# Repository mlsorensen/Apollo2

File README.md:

# Apollo 2

<!-- One logo for both GitHub themes: dark ink on a solid white silhouette
     with a white halo around the outside, so it reads on white (fill and halo
     invisible) and on a dark page (a light bust with a glow). A <picture> +
     prefers-color-scheme switch was tried and follows the BROWSER's colour
     scheme, not the GitHub theme: Safari on a dark-mode Mac served the white
     logo onto a light GitHub page. -->

Firmware project that turns a small ESP32 touchscreen into a local
controller for a **La Marzocco Micra** espresso machine — over Bluetooth, with
no cloud dependency for day‑to‑day use.

Set your brew temperature, flip the steam boiler, put the machine on standby,
watch the boiler come up to temperature, and (with a supported Bluetooth scale)
run a live shot timer and flow graph — all from a dedicated little screen next
to the machine instead of a phone app.

> The focus is on local control via bluetooth. Currently internet is only used for optional NTP.

**Contents:**
[Features](#features) ·
[Getting started](#getting-started) ·
[Screenshots](#screenshots) ·
[Supported hardware](#supported-hardware) ·
[3D prints](#3d-prints) ·
[Developer documentation](#developer-documentation) ·
[Credits](#credits) ·
[License](#license)

---

## Features

- **Local Micra control over Bluetooth** — brew and steam temperatures, steam
  boiler on/off, standby, and live machine status. No cloud, no phone app.
- **Bluetooth scales** — Bookoo Themis, Acaia (Umbra, Lunar, Prochef, Pyxis)
  and Varia Aku: live weight, shot timer, flow graph, tare, and the scale's
  own settings from the screen. A second, **bench** scale for the counter
  shows its weight on Home too — in the scale card or beside the graph —
  and, with **Record dose** turned on, records your dose for the next shot
  (or set a default dose), so the graph and History show the brew ratio.
- **Brew by weight** — stop the shot at a target weight on boards wired into
  the paddle circuit, or detect shots from the weight stream alone on any
  board. Finished shots freeze into a review graph.
- **Group care** — auto‑flush after the cup lifts, flush on demand, and a
  backflush cleaning cycle, on wired boards.
- **Warm‑up chime** — boards with a speaker play a tune when the machine is
  ready, so you can start it and walk away.
- **Schedule** — switch the machine on (with a warm‑up lead) and back to
  standby at set times, the same every day or per weekday, from the device's
  own NTP clock. **Auto‑standby** sends it to standby a set time after the
  last shot, independent of the schedule.
- **Shot history** — every shot is saved to a microSD card as CSV, browsable on
  the device's Stats tab or from a phone via the device's own web page.
- **Settings backup** — preferences copy to the same card and restore onto
  replacement hardware.
- **Over‑the‑air updates** — the device checks for new firmware and installs
  it on request, with an optional beta channel.
- **Setup from your phone, no app** — pairing and Wi‑Fi credentials go in
  through a page the device serves itself; scan the QR code on its screen.
- **Automatic time** — NTP over your Wi‑Fi with a timezone picker, saved to
  the on‑board RTC where present.
- **Made to live on the counter** — themes, °C/°F, 12/24‑hour clock,
  brightness, idle‑screen artwork; layouts from 4.3" to 8" panels.

Everything keeps working if the machine, the scale, or Wi‑Fi is absent — the
UI just shows that part as offline.

---

## Getting started

> [!IMPORTANT]
> **Before buying any hardware, confirm you can get your machine's Bluetooth
> token.** Apollo authenticates to the Micra with a token issued by the La
> Marzocco cloud. Grab it first with the **[LM Token](tools/lmtoken/)** app — sign
> in with your La Marzocco account and copy the token. If it comes back blank, the
> same tool can provision one over Bluetooth. Checking now avoids a nasty surprise
> after a board is already on your bench.

**Prefer to watch?** [Apollo 2 for Micra — From Setup to Shot](https://youtu.be/2J9Y8xyeB9w)
walks through choosing a board, flashing it and setting it up, start to first shot.

### 1. Get the hardware

Pick a board from the **[Which board?](#which-board)** table below — three of
them come as finished boxes that need no assembly at all. A Bluetooth scale is
optional but unlocks the shot timer, flow graph, and brew‑by‑weight. Wiring
the machine's paddle (for Auto shot) is optional too, and can always be added
later — see the [wiring guide](docs/WIRING.md) (which also covers the
optional Apollo Link board — **P4 boards only**, not the S3‑4.3C).

### 2. Flash the firmware

**No-toolchain option:** the [web flasher](https://mlsorensen.github.io/Apollo2/)
flashes any supported board straight from Chrome, Edge, or Firefox over USB —
pick your board, click Install. (The P4‑5 and P4‑4.3 exist with two ESP32‑P4
chip revisions that need different images; boards bought before about August
2026 are v1.x, newer ones v3. **Detect board** reads it off a device already
running Apollo; on a blank board pick it on the card. A wrong pick just won't
boot until the other image is flashed.) Upgrading this way keeps your paired machine,
Wi‑Fi and settings (unless you choose "Erase device"). Prebuilt images also live
on the [Releases](https://github.com/mlsorensen/Apollo2/releases) page — those
are full images, so flashing one with `esptool` *does* clear saved settings.

Until a Micra is paired, the device opens on a welcome screen with the three
recommended steps: **Set up WiFi** (network and time zone from your phone;
sets the clock and enables updates), **Pair Micra**, and **Pair scale**. All
are optional — **Later** skips it until the next power‑up, **Don't show
again** for good; every step is in Settings too.

After the first flash Apollo updates itself over WiFi: it checks for new
firmware, shows what changed, and installs on a tap. Tick **Include
pre-releases** on the flasher (or turn on **Settings → Apollo → WiFi → Beta
updates** on the device) to run beta builds instead — testing welcome, and a
build that won't boot rolls back on its own.

Building from source requires [PlatformIO](https://platformio.org/) (`pio`) and
a USB cable.

```sh
make flash            # print selection of flash options
make flash-p4-5       # or target a board: p4-5 | p4-4-3 | s3-4-3c | p4-x-8
                      # (P4-5 / P4-4.3 come with two chip revisions needing different
                      #  images; these targets read the chip and pick the right one)
make monitor          # open the serial console (115200 baud)
```

### 3. Pair the machine

**Settings → Micra → Bluetooth → Scan**, then pick your machine. The device saves
it, then asks for the machine's **Bluetooth token** (step 4) — the token is issued
by the La Marzocco cloud and can't be read off the machine, so there's a short
one‑time step to fetch it.

### 4. Enter your token

Tap **Enter token** on the prompt (or **Settings → Micra → Set up**) to start the
device's own Wi‑Fi access point, **`Micra-Setup`**. Scan the QR code on the
device's screen with your phone's camera — it joins the access point and the
setup page pops up on its own. (Or join `Micra-Setup` manually and open
**http://192.168.4.1**.) Paste your token and Save — the device connects and the
access point closes on its own.

Where to get the token:

- Download the **LM Token** app for your OS from the [Releases](../../releases)
  page, unzip, and double-click it. Sign in with your La Marzocco account, pick
  your machine, and hit **Copy token**. This is the only step that uses the
  internet, and it runs on your computer. (Prefer a terminal? The `lmtoken` CLI
  is on the same page.)

> Prefer to build **LM Token** / `lmtoken` from source (Go), or script it? See
> [`tools/lmtoken/README.md`](tools/lmtoken/README.md).

### 5. (Optional) Wi‑Fi + automatic time

On the same setup page you can enter your home Wi‑Fi name and password. The
device then joins your network, gets an IP, and syncs the clock over NTP. Pick
your city under **Settings → Apollo → WiFi → Timezone**. Auto‑sync can be turned
off there too (**Auto time (NTP)**).

Because the setup page is always reachable from **Set up WiFi**, you can never be
locked out if your network changes.

### 6. Find your way around

- **Home** shows the machine (and scale, if paired). The large action button is
  Standby / Turn On when connected, and becomes a **Connect** button when the
  machine is disconnected. With a scale, the pill under the shot timer cycles
  the shot mode — **Auto shot** (wired paddle boards) / **Shot detect** /
  **Manual** — and becomes **Reset** while a finished shot is up for review.
- **Settings** groups everything under Micra, Scale, and Device (brightness,
  clock, units, theme, Wi‑Fi).
- **Stats** shows brew/boiler temperature history, the shot **History** log
  (SD‑card boards), and device info.

Every screen and setting is described in the **[user manual](MANUAL.md)** —
it opens with a **map of every screen and setting** if you're looking for
where something lives.

---

## Screenshots

<!-- These are curated copies of the simulator's output — see "The simulator"
     under Developer documentation for the refresh convention. -->

---

## Supported hardware

The firmware targets Waveshare ESP32 touch boards. One board is selected at
build time.

### Which board?

Four boards are supported, and each has its own firmware image. Every one of
them delivers the full brew‑by‑weight experience with **zero wiring** (via Shot
detect); the wiring column only matters if you *also* want **Auto shot** — the
wired‑paddle mode where the machine's own paddle starts the shot and the
firmware cuts it at target weight.

| Pick | Best for | Screen | Enclosure | Auto‑shot wiring *(optional)* | Performance |
|------|----------|--------|-----------|-------------------------------|-------------|
| [ESP32‑P4‑WIFI6‑Touch‑LCD‑5](https://www.waveshare.com/esp32-p4-wifi6-touch-lcd-5.htm) (SKU 33762) | **Mounting on the Micra** | 5" 1280×720 | [3D‑printed shell](hardware/3d-prints/) | DIY cable with an external opto module | **Best** |
| [ESP32‑P4‑WIFI6‑Touch‑LCD‑4.3](https://www.waveshare.com/esp32-p4-wifi6-touch-lcd-4.3.htm) | **Mounting on the Micra, smaller screen** | 4.3" 800×480 | [3D‑printed shell](hardware/3d-prints/) | DIY cable with an external opto module | **Best** |
| [ESP32‑S3‑Touch‑LCD‑4.3C **BOX**](https://www.waveshare.com/esp32-s3-touch-lcd-4.3c.htm?sku=33630) (SKU 33630) | **Mounting on the Micra with nothing to build** | 4.3" 800×480 | Finished box | **Built‑in opto** — three wires into screw terminals, nothing to build (the optional Apollo Link board is P4‑only and does not fit this box) | Good |
| [ESP32‑P4‑WIFI6‑Touch‑LCD‑X **8" box**](https://www.waveshare.com/esp32-p4-wifi6-touch-lcd-7-8-10.1.htm) | **Counter‑top companion** | 8" 1280×800 | Finished box | DIY cable with an external opto module | **Best** |

**Start with the ESP32‑P4‑WIFI6‑Touch‑LCD‑5.** It's the recommended
mount‑on‑the‑Micra option: the P4 is much faster than the S3 (32 MB flash +
32 MB PSRAM against 16/8), and the 5" panel is the right size on the machine.
The cost is two bits of DIY — you print a [shell](hardware/3d-prints/), and if
you want Auto shot you make up a cable with an external opto module.

**The ESP32‑P4‑WIFI6‑Touch‑LCD‑4.3 is the same board with a smaller screen.**
Identical electronics — same processor, radio, audio, battery path, SD slot and
paddle wiring; only the panel differs (4.3" 800×480 instead of 5" 1280×720).
Pick between the two on **screen size and a small price difference**, nothing
else. It takes its own [printed shell](hardware/3d-prints/) and its own
firmware image.

**Choose the S3‑4.3C BOX if you'd rather not print a case or build a cable.** It's the
only small board that arrives as a finished box *and* has the opto‑isolators
built in, so Auto shot is three wires into screw terminals with no cable to
assemble — genuinely the least‑hacking route to a fully wired setup. The
trade is speed: it's the slower part. (The [wiring guide](docs/WIRING.md)
covers both styles.)

**The X 8" box is the counter‑top companion** — the same P4 electronics behind
the biggest screen, in a finished enclosure, for sitting beside the machine
rather than on it. Verified on hardware.

Power, battery and RTC notes live in
**[docs/HARDWARE.md](docs/HARDWARE.md)**.

### 3D‑printed stand, shells and mounts

Ready‑to‑print 3MF files live in [`hardware/3d-prints/`](hardware/3d-prints/):

| File | What it is |
|------|------------|
| [`apollo2-stand.3mf`](hardware/3d-prints/apollo2-stand.3mf) | Counter‑top **stand**. Mounts the S3‑4.3C‑BOX directly (it has the matching holes), and every shell below mounts to it the same way. |
| [`apollo2-magnet-mount.3mf`](hardware/3d-prints/apollo2-magnet-mount.3mf) | Optional **magnet mount** — attaches the device to the Micra's top corner instead of the counter. |
| [`apollo2-wiring-gasket.3mf`](hardware/3d-prints/apollo2-wiring-gasket.3mf) | Optional **wiring gasket** — spaces the Micra's cover so the wiring can run underneath it. |
| [`esp32-p4-5-shell.3mf`](hardware/3d-prints/esp32-p4-5-shell.3mf) | Shell for the **ESP32‑P4‑WIFI6‑Touch‑LCD‑5**. |
| [`esp32-p4-5-shell-slim.3mf`](hardware/3d-prints/esp32-p4-5-shell-slim.3mf) | Slimmer shell for the **ESP32‑P4‑WIFI6‑Touch‑LCD‑5** — no battery compartment (USB‑power only). |
| [`esp32-p4-4.3-shell.3mf`](hardware/3d-prints/esp32-p4-4.3-shell.3mf) | Shell for the **ESP32‑P4‑WIFI6‑Touch‑LCD‑4.3**. |
| [`esp32-p4-x-8-backplate.3mf`](hardware/3d-prints/esp32-p4-x-8-backplate.3mf) | Backplate that adapts the **ESP32‑P4‑WIFI6‑Touch‑LCD‑X 8" box** to the counter‑top stand above. |

This [short video](https://youtube.com/shorts/Ea0IaJ7hjvQ) shows how the
magnet mount and wiring gasket fit together on the machine.

Fasteners:

- **Shells**: 8 × **M2.5×0.45, 5 mm** screws each — 4 fasten the board into
  the shell, 4 fasten the shell cover.
- **Stand mount**: 2 × **M4‑0.7×8 mm** screws — same spec whether you're
  mounting the S3‑4.3C‑BOX or any of the printed shells.
- **Magnet mount**: 8 × **10 mm × 3 mm** neodymium disc magnets.

---

## Developer documentation

### Architecture

The code is layered so the same UI runs on a real board and on a laptop:

```
include/core/        Pure interfaces (ports) + domain types. No LVGL, Arduino,
                     BLE, or SDL — just C++ and structs. e.g. IMachine, IScale,
                     IClock, INetwork, IProvisioner, IBrewController, IShotStore
                     (SD shot history), and the BLE central port (ble::ICentral).

src/core/            Portable protocol logic: the La Marzocco Micra link and
                     the Bookoo scale driver, written only against ble::ICentral
                     — so a new platform (Linux/BlueZ, Pico/btstack) reuses the
                     Bluetooth protocol code unchanged and implements only the
                     transport. Also the device-independent decisions: which
                     event makes which sound (sound.cpp), when a warm-up counts
                     as finished (ready_chime.h).

src/ui/              The LVGL user interface. Depends ONLY on core/ interfaces,
                     never on a concrete platform. Portable.

src/platform_esp32/  Device implementations of the core ports: the NimBLE GATT
                     transport, NVS config, display/touch drivers, Wi-Fi
                     station + NTP, the setup-portal web server.

src/platform_host/   "Fake" implementations that feed canned data, so the UI can
                     be built and rendered on a host with no hardware.

src/device/main.cpp  Device entry: wires the real implementations to ui::App.
src/sim/main.cpp     Simulator entry: wires the fakes, renders frames to PNG.
```

The UI is written against the `core::` ports and is injected with concrete
implementations at startup (`App::build(...)`). Swapping the real BLE machine for
a `FakeMachine` is all that separates a board build from a laptop render — the UI
code is byte‑for‑byte identical.

### The simulator

No hardware needed. Builds a native executable that renders each screen/layout
to `renders/*.png`:

```sh
make sim              # build + run, writes renders/*.png
```

This is the fastest way to iterate on UI: change code, `make sim`, look at the
PNGs. Every supported screen size and several states are rendered.

The `renders/` folder is git‑ignored build output; the screenshots in
`docs/img/` are curated copies, and the annotated manual images in
`docs/img/manual/` are generated from renders by `make docs-img`
(`tools/annotate_docs.py` + its manifest). **When the UI changes, run
`make sim`, refresh the affected `docs/img/*.png`, and re-run `make docs-img`
as part of the same change** so the README and manual stay accurate.

### Prerequisites

**PlatformIO** (`pip install platformio`) builds everything, and **node** (any
recent LTS — `brew install node`) builds the shot-history web page the device
serves. That page is embedded in the firmware as a generated header,
`include/platform_esp32/webapp_dist.h`, which is **not committed**: every
`make build`/`make flash` target rebuilds it when anything under
[`tools/webapp/`](tools/webapp) changes, and the release workflow does the same,
so a board can never serve a page that has drifted from the source. `make sim`
needs no node — the simulator has no web server.

### Building directly

`pio run` does *not* generate the web-app header (that dependency lives in the
Makefile), so run `make webapp` first — or just use the `make` targets, which
handle it.

```sh
pio run -e esp32-p4-micra-5       # 5"   1280x720 (P4, MIPI-DSI, WiFi6/BLE via C6)
pio run -e esp32-p4-micra-43      # 4.3"  800x480 (P4, MIPI-DSI, same board as the 5)
pio run -e esp32-p4-micra-5-rev3  # the same two boards on the v3 ESP32-P4 silicon
pio run -e esp32-p4-micra-43-rev3 #   (shipping since ~Aug 2026; a separate image)
pio run -e esp32-s3-micra-4-3c    # 4.3"  800x480 (S3, RGB panel)
pio run -e esp32-p4-micra-x-8     # X-series 8" box (P4, 1280x800)
pio run -e sim                    # native simulator
```

`platformio.ini` also carries a few envs for boards that aren't released — they
build, and they're kept as the record of how those boards differ. `make
build-release` compiles the six published images (four products, the two P4
boards in both silicon revisions); `make build-all` compiles
every env.

Build environments and per‑board flags live in
[`platformio.ini`](platformio.ini); the pin/panel definitions for each board are
in [`include/platform_esp32/board_config.h`](include/platform_esp32/board_config.h).

### Adding a board

Add an `#elif defined(BOARD_...)` block in `board_config.h` with the same
constant names the drivers read (pins, panel size, feature macros), then add a
matching `[env:...]` in `platformio.ini` with the `-DBOARD_...` flag. Driver code
never hardcodes a pin — it reads `board::` constants — so a new board is mostly a
config block.

That makes the board *buildable*, not *supported*. Releasing one is a separate,
deliberate step: a row in the `.github/workflows/firmware-release.yml` matrix
(whose `board` value must equal the block's `kUpdateSlug`, since the
self‑updater fetches `<site>/<tag>/firmware/app/<slug>.bin`), a card in
`site/index.html`, and a row in the tables above. (The flasher's engine,
esp-web-tools, is vendored by `tools/build_esp_web_tools.sh` with a pinned
esptool-js rather than loaded from unpkg — the script says why.) Releases are
tagged `vX.Y.Z`;
a `vX.Y.Z-beta.N` tag publishes the same images as a pre-release, listed only in
`releases-beta.json` (the stable `releases.json` every device reads stays
releases-only) — promoting one to stable is a rebuild at the real tag, never a
copy of the artifacts, because `fw::kVersion` is compiled into the image.
Publishing is gated: the workflow builds unattended, but the jobs that create
the Release and push `gh-pages` (the OTA origin) run in a protected
environment that holds the only write credential and waits for the owner's
approval, and repository rulesets let only an admin touch `gh-pages` or a
`v*` tag. Several envs stay on the
buildable side on purpose.

### Repository layout

```
include/core/          Domain interfaces + types
src/core/              Portable protocol implementations (Micra BLE, scales,
                       audio cues)
include/platform_esp32/ Device driver headers + board_config.h
include/platform_host/  Host fakes
include/ui/             UI headers (widgets, screen profiles, timezones)
include/vendor/         Vendored third-party headers (stb_image_write)
src/                    Implementations (see Architecture above)
hardware/3d-prints/     Printable stand, board shells + mounts (3MF)
docs/adr/               Decision and engineering log: why things are built
                        the way they are, with the bench evidence
tools/                  sim.sh, flash.sh, lmtoken (Go), PlatformIO helper scripts
renders/                Simulator output (PNG)
```

---

## Credits & third‑party

This project stands on the work of others. Grateful thanks to:

- **[pylamarzocco](https://github.com/zweckj/pylamarzocco)** by Josef Zweck
  (MIT) — the reference for La Marzocco's Bluetooth protocol (GATT
  characteristic UUIDs, the JSON command/state payloads, machine name prefix) and
  the cloud auth flow that `tools/lmtoken` re‑implements in Go.
- **[goscale](https://github.com/mlsorensen/goscale)** (Apache‑2.0) — the model
  for the scale interface and the Bookoo Themis notification decode.
- **[apollo](https://github.com/mlsorensen/apollo)** — brew‑by‑weight /
  paddle‑stop approach that inspires the (in‑progress) brew controller.
- **Waveshare** — board bring‑up details and register maps for the CH422G IO
  expander, GT911 / CST816 touch controllers, and the RGB panel timings, from
  their published ESP32‑S3 demos.
- **[stb_image_write](https://github.com/nothings/stb)** by Sean Barrett (public
  domain / MIT) — vendored in `include/vendor/` for PNG output in the simulator;
  its license is retained in the file.

Library dependencies (fetched by PlatformIO): **LVGL** (MIT), **NimBLE‑Arduino**
(Apache‑2.0), **Arduino‑ESP32** (LGPL‑2.1 / Apache‑2.0), **GFX Library for
Arduino** (BSD‑style), and **ArduinoJson** (MIT). Each retains its own license.

---

## License

[MIT](LICENSE) © 2026 Marcus.

Not affiliated with or endorsed by La Marzocco. "La Marzocco" and "Micra" are
trademarks of their respective owner; used here only to describe compatibility.

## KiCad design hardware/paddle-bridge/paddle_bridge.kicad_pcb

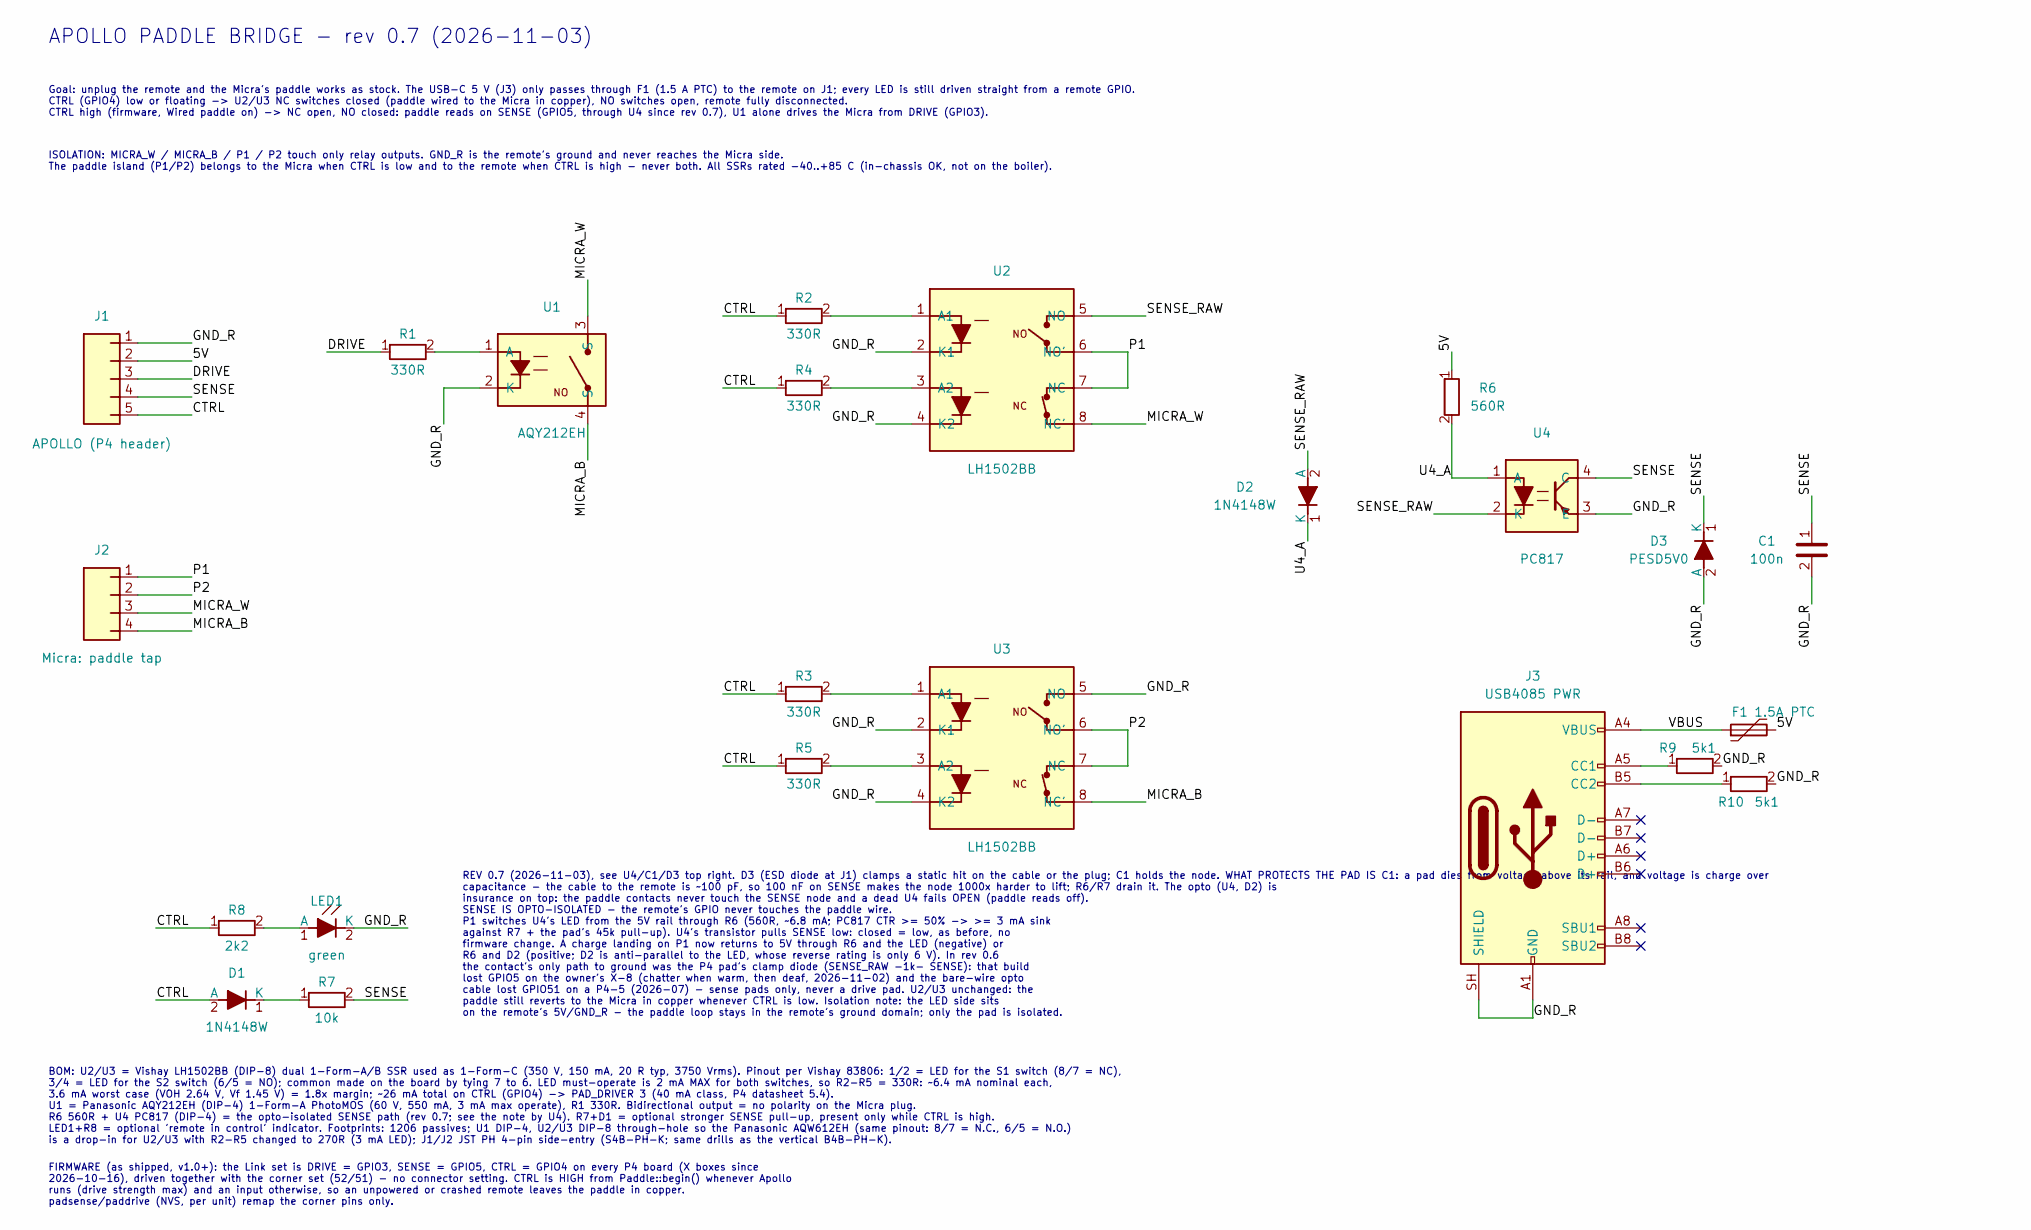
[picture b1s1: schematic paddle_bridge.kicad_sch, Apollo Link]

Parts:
C1: 100n; C_1206_3216Metric
D1, D2: 1N4148W; D_1206_3216Metric
D3: PESD5V0; D_SOD-323
F1: 1.5A PTC; Fuse_1812_4532Metric
J1: APOLLO (P4 header); JST_PH_S5B-PH-K_1x05_P2.00mm_Horizontal
J2: Micra: paddle tap; JST_PH_S4B-PH-K_1x04_P2.00mm_Horizontal
J3: USB4085 PWR; USB_C_Receptacle_GCT_USB4085
LED1: green; LED_1206_3216Metric
R1, R2, R3, R4, R5: 330R; R_1206_3216Metric
R6: 560R; R_1206_3216Metric
R7: 10k; R_1206_3216Metric
R8: 2k2; R_1206_3216Metric
R9, R10: 5k1; R_1206_3216Metric
U1: AQY212EH; DIP-4_W7.62mm
U2, U3: LH1502BB; DIP-8_W7.62mm
U4: PC817; DIP-4_W7.62mm

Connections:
/5V: F1.2, J1.2, R6.1
/CTRL: D1.2 (A), J1.5, R2.1, R3.1, R4.1, R5.1, R8.1
/DRIVE: J1.3, R1.1
/GND_R: C1.2, D3.2 (A), J1.1, J3.A1 (GND), J3.A12 (GND), J3.B1 (GND), J3.B12 (GND), J3.SH (SHIELD), LED1.2 (K), R9.2, R10.2, U1.2 (K), U2.2 (K1), U2.4 (K2), U3.2 (K1), U3.4 (K2), U3.5 (NO), U4.3 (E)
/MICRA_B: J2.4, U1.4 (S), U3.8 (NC')
/MICRA_W: J2.3, U1.3 (S), U2.8 (NC')
/P1: J2.1, U2.6 (NO'), U2.7 (NC)
/P2: J2.2, U3.6 (NO'), U3.7 (NC)
/SENSE: C1.1, D3.1 (K), J1.4, R7.2, U4.4 (C)
/SENSE_RAW: D2.2 (A), U2.5 (NO), U4.2 (K)
/U4_A: D2.1 (K), R6.2, U4.1 (A)
/VBUS: F1.1, J3.A4 (VBUS), J3.A9 (VBUS), J3.B4 (VBUS), J3.B9 (VBUS)
unnamed: D1.1 (K), R7.1
unnamed: J3.A5 (CC1), R9.1
unnamed: J3.B5 (CC2), R10.1
unnamed: LED1.1 (A), R8.2
unnamed: R1.2, U1.1 (A)
unnamed: R2.2, U2.1 (A1)
unnamed: R4.2, U2.3 (A2)
unnamed: R3.2, U3.1 (A1)
unnamed: R5.2, U3.3 (A2)

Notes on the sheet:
Goal: unplug the remote and the Micra's paddle works as stock. The USB-C 5 V (J3) only passes through F1 (1.5 A PTC) to the remote on J1; every LED is still driven straight from a remote GPIO. CTRL (GPIO4) low or floating -> U2/U3 NC switches closed (paddle wired to the Micra in copper), NO switche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
BOM: U2/U3 = Vishay LH1502BB (DIP-8) dual 1-Form-A/B SSR used as 1-Form-C (350 V, 150 mA, 20 R typ, 3750 Vrms). Pinout per Vishay 83806: 1/2 = LED for the S1 switch (8/7 = NC), 3/4 = LED for the S2 switch (6/5 = NO); common made on the board by tying 7 to 6. LED must-operate is 2 mA MAX for both sw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
APOLLO PADDLE BRIDGE - rev 0.7 (2026-11-03)
FIRMWARE (as shipped, v1.0+): the Link set is DRIVE = GPIO3, SENSE = GPIO5, CTRL = GPIO4 on every P4 board (X boxes since 2026-10-16), driven together with the corner set (52/51) - no connector setting. CTRL is HIGH from Paddle::begin() whenever Apollo runs (drive strength max) and an input otherwi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
ISOLATION: MICRA_W / MICRA_B / P1 / P2 touch only relay outputs. GND_R is the remote's ground and never reaches the Micra side. The paddle island (P1/P2) belongs to the Micra when CTRL is low and to the remote when CTRL is high - never both. All SSRs rated -40..+85 C (in-chassis OK, not on the boil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
REV 0.7 (2026-11-03), see U4/C1/D3 top right. D3 (ESD diode at J1) clamps a static hit on the cable or the plug; C1 holds the node. WHAT PROTECTS THE PAD IS C1: a pad dies from voltage above its rail, and voltage is charge over capacitance - the cable to the remote is ~100 pF, so 100 nF on SENSE ma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

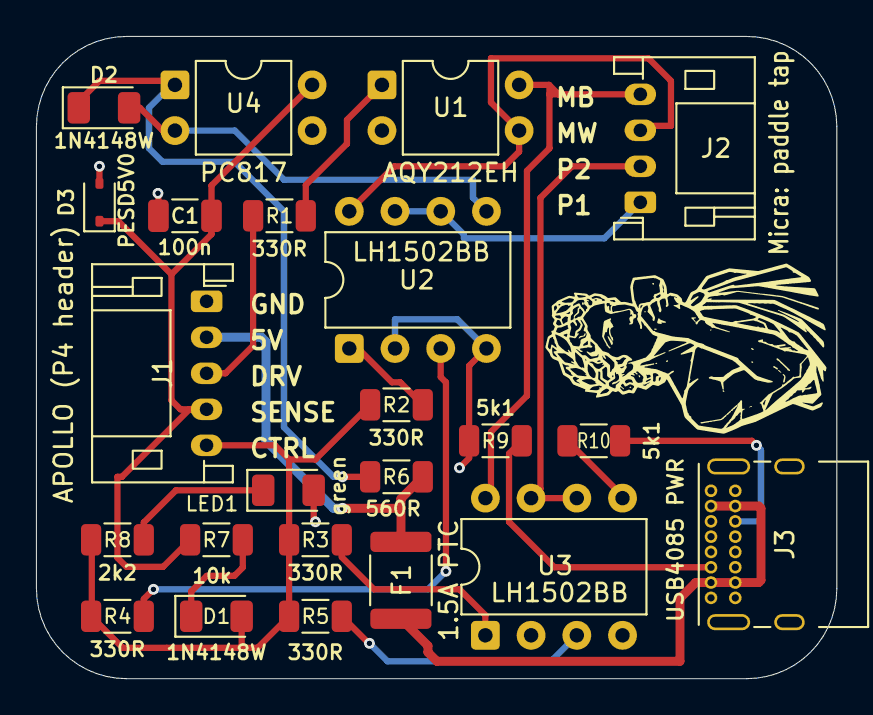
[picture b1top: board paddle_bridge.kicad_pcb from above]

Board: 2 copper layers, 44.5 x 35.7 mm, 23 parts (0 on the bottom side), 21 nets.
